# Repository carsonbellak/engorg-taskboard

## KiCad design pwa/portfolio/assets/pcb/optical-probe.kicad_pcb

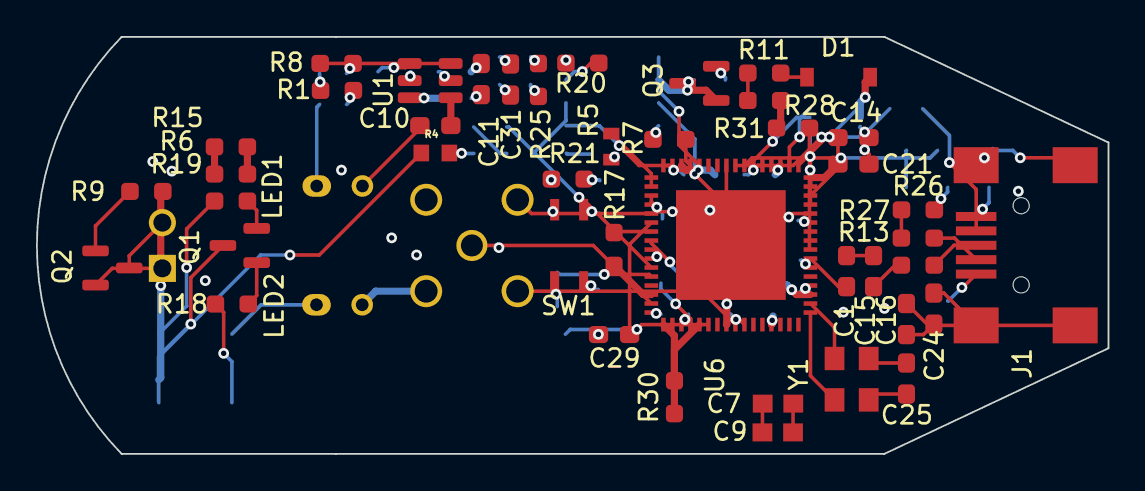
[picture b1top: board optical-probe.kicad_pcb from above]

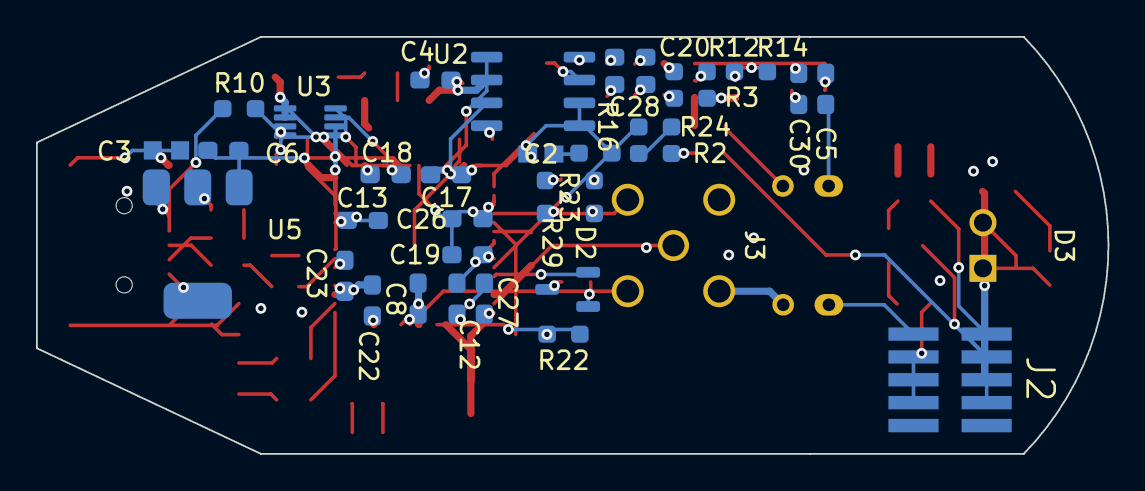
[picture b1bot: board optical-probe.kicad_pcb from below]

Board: 4 copper layers, 59.5 x 23.2 mm, 81 parts (35 on the bottom side), 123 nets.

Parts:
C1, C2, C3, C4, C5, C6, C7, C8, C9, C10, C11, C12, C13, C14, C15, C16, C17, C18, C19, C20, C21, C22, C23, C24, C25, C26, C27, C28, C29, C30, C31: Part
D1, D2, D3: Part
J1, J2, J3: Part
LED1, LED2: Part
Q1, Q2, Q3: Part
R1, R2, R3, R4, R5, R6, R7, R8, R9, R10, R11, R12, R13, R14, R15, R16, R17, R18, R19, R20, R21, R22, R23, R24, R25, R26, R27, R28, R29, R30, R31: Part
SW1: Part
U1, U2, U3, U4, U5, U6: Part
Y1: Part

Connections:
NET1: R3.2, U1.6
NET2: C18.1, U6.19
NET3: R21.2, R29.2
NET4: C13.1, U6.11
NET5: C23.2, U6.6
NET6: C1.1, C15.1
NET7: C26.1, U6.35
NET8: C21.2, U6.16
NET9: R17.2, U6.39
NET10: R26.1, R27.2
NET11: C23.1, U6.4
NET12: D3.2, Q2.3
NET13: C10.1, U1.1
NET14: C26.2, U6.36
NET15: R2.2, R4.2
NET16: C12.2, U6.51
NET17: C8.1, U6.58
NET18: R23.1, SW1.3
NET19: Q1.1, R18.1
NET20: C11.2, R12.2
NET21: R30.2, U6.53
NET22: C2.2, R5.1
NET23: C16.1, J1.8
NET24: C7.2, C9.2
NET25: C7.1, C9.1
NET26: C17.1, U6.32
NET27: J1.4, U5.3
NET28: J1.1, U5.2
NET29: R28.1, R31.1
NET30: C1.2, U6.7
NET31: C11.1, R3.1
NET32: C8.2, U6.56
NET33: C20.1, C31.1
NET34: Q2.1, R9.2
NET35: C4.1, Q3.2
NET36: R30.1, U6.49
NET37: C13.2, U6.12
NET38: R11.2, R28.2
NET39: J1.3, R13.1
NET40: J1.2, R27.1
NET41: U3.1, U6.13
NET42: R20.2, U2.8
NET43: R26.2, U5.2
NET44: C19.1, U6.42
NET45: C14.1, U6.14
NET46: C28.2, C31.2
NET47: J2.4, R18.2
NET48: R29.1, SW1.4
NET49: R14.2, U1.5
NET50: C25.1, Y1.3
NET51: R7.2, U6.29
NET52: D3.1, Q2.2
NET53: C22.2, U6.3
NET54: C3.2, J1.7
NET55: C27.2, U6.48
NET56: C22.1, U6.61
NET57: C14.2, U3.7
NET58: D2.1, SW1.2
NET59: R20.1, U2.7
NET60: C30.1, R1.2
NET61: C3.1, J1.9
NET62: C16.2, C24.2
NET63: C17.2, U6.30
NET64: R2.1, R24.1
NET65: J2.9, R19.1
NET66: C10.2, LED1.2
NET67: C29.1, R22.2
NET68: J2.5, R9.1
NET69: C15.2, R13.2
NET70: C28.1, R25.1
NET71: R7.1, U2.4
NET72: J3.5, LED2.2
NET73: Q1.2, R19.2
NET74: D2.3, SW1.1
NET75: U6.2, Y1.1
NET76: C27.1, U6.52
NET77: C25.2, Y1.4
NET78: C18.2, U6.21
NET79: C24.1, J1.6
NET80: C12.1, U6.40
NET81: J2.10, LED2.1
NET82: R17.1, U6.46
NET83: C4.2, Q3.3
NET84: R12.1, U1.2
NET85: R16.2, U2.6
NET86: R5.2, U6.34
NET87: C5.2, LED1.1
NET88: Q3.1, U2.2
NET89: R6.1, R15.2
NET90: D1.2, R11.1
NET91: C21.1, U3.8
NET92: R31.2, U6.8
NET93: C19.2, U6.25
NET94: C2.1, R16.1
NET95: C6.1, U5.1
NET96: U3.4, U6.18
NET97: D2.2, U6.44
NET98: R21.1, R23.2
NET99: U3.2, U6.15
NET100: U6.1, Y1.2
NET101: C29.2, U6.38
NET102: U2.3, U6.65
NET103: J2.3, Q1.3
NET104: D1.1, U3.6
NET105: R6.2, R15.1
NET106: J2.7, R4.1
NET107: R22.1, U6.54
NET108: U2.5, U6.31
NET109: U2.1, U6.28
NET110: C5.1, R1.1
NET111: U3.3, U6.24
NET112: U3.5, U6.17
NET113: J3.3, U6.37
NET114: R10.1, U6.22
NET115: C6.2, U6.23
NET116: R14.1, U1.4
NET117: J3.1, U6.47
NET118: C20.2, R25.2
NET119: J3.4, U6.57
NET120: J1.5, R10.2
NET121: R24.2, U6.43
NET122: C30.2, R8.1
NET123: R8.2, U1.3
